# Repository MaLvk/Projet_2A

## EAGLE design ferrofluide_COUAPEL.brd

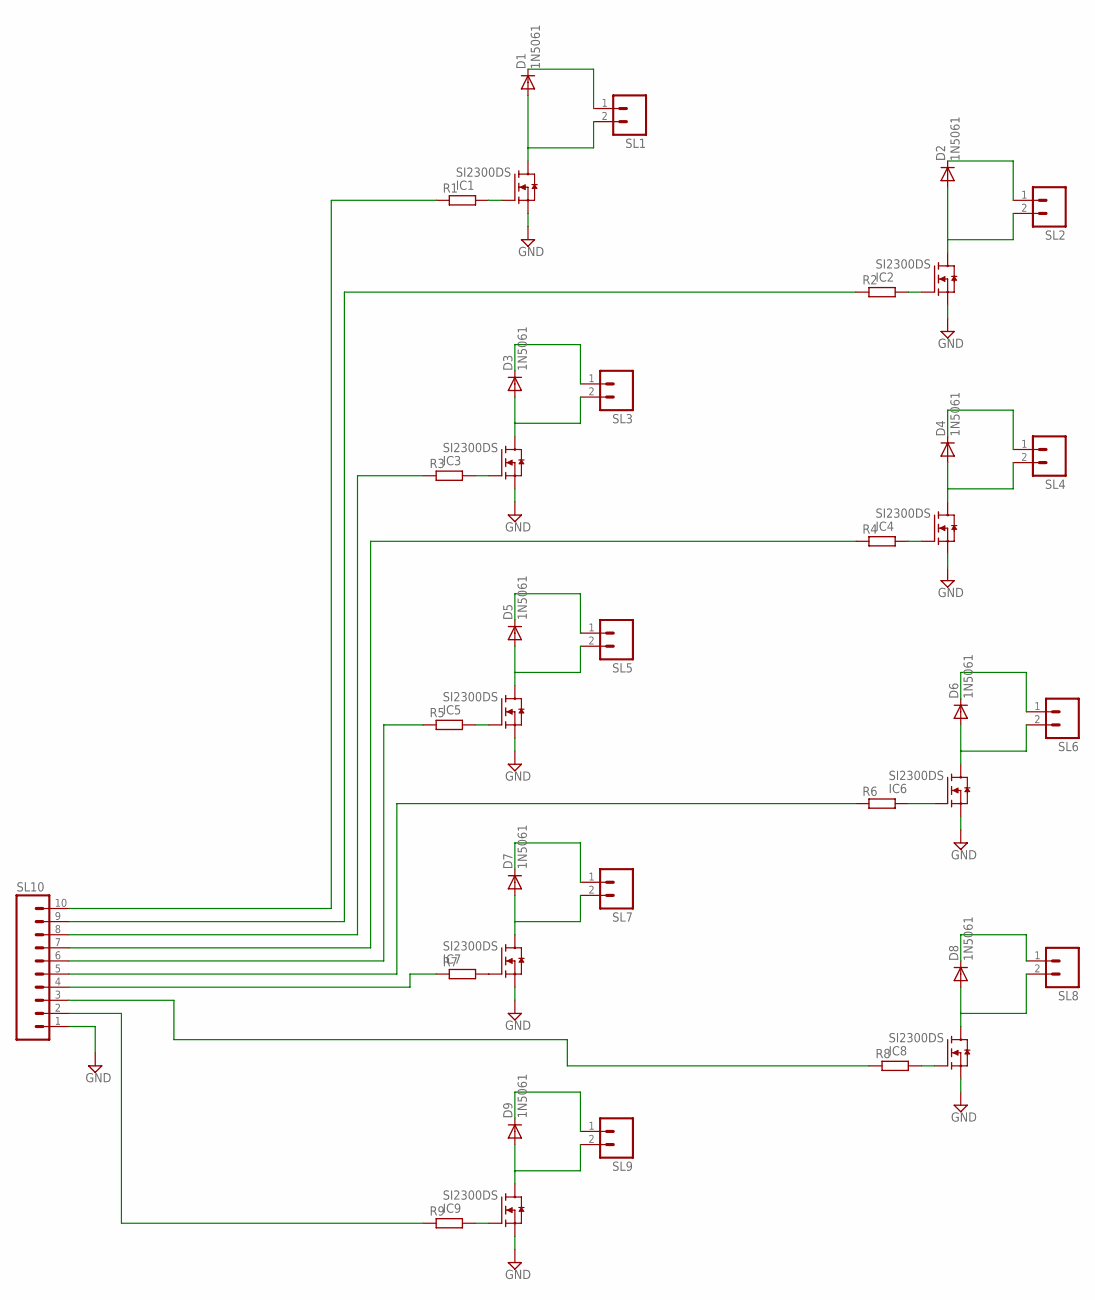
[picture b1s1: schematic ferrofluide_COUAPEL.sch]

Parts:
D1, D2, D3, D4, D5, D6, D7, D8, D9: 1N5061; SOD57-10
IC1, IC2, IC3, IC4, IC5, IC6, IC7, IC8, IC9: SI2300DS; SOT23
R1, R2, R3, R4, R5, R6, R7, R8, R9: R-EU_0207/12; 0207/12
SL1, SL2, SL3, SL4, SL5, SL6, SL7, SL8, SL9: M02; 02P
SL10: M10; 10P

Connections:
GND: IC1.2 (S), IC2.2 (S), IC3.2 (S), IC4.2 (S), IC5.2 (S), IC6.2 (S), IC7.2 (S), IC8.2 (S), IC9.2 (S), SL10.1
unnamed: D1.C, SL1.1
unnamed: D1.A, IC1.3 (D), SL1.2
unnamed: IC1.1 (G), R1.2
unnamed: D2.C, SL2.1
unnamed: D2.A, IC2.3 (D), SL2.2
unnamed: IC2.1 (G), R2.2
unnamed: D4.C, SL4.1
unnamed: D4.A, IC4.3 (D), SL4.2
unnamed: IC4.1 (G), R4.2
unnamed: D6.C, SL6.1
unnamed: D6.A, IC6.3 (D), SL6.2
unnamed: IC6.1 (G), R6.2
unnamed: D8.C, SL8.1
unnamed: D8.A, IC8.3 (D), SL8.2
unnamed: IC8.1 (G), R8.2
unnamed: R9.1, SL10.2
unnamed: D9.C, SL9.1
unnamed: D9.A, IC9.3 (D), SL9.2
unnamed: D7.C, SL7.1
unnamed: IC9.1 (G), R9.2
unnamed: R8.1, SL10.3
unnamed: D7.A, IC7.3 (D), SL7.2
unnamed: IC7.1 (G), R7.2
unnamed: D5.C, SL5.1
unnamed: D5.A, IC5.3 (D), SL5.2
unnamed: IC5.1 (G), R5.2
unnamed: D3.C, SL3.1
unnamed: D3.A, IC3.3 (D), SL3.2
unnamed: IC3.1 (G), R3.2
unnamed: R7.1, SL10.4
unnamed: R6.1, SL10.5
unnamed: R5.1, SL10.6
unnamed: R4.1, SL10.7
unnamed: R3.1, SL10.8
unnamed: R2.1, SL10.9
unnamed: R1.1, SL10.10

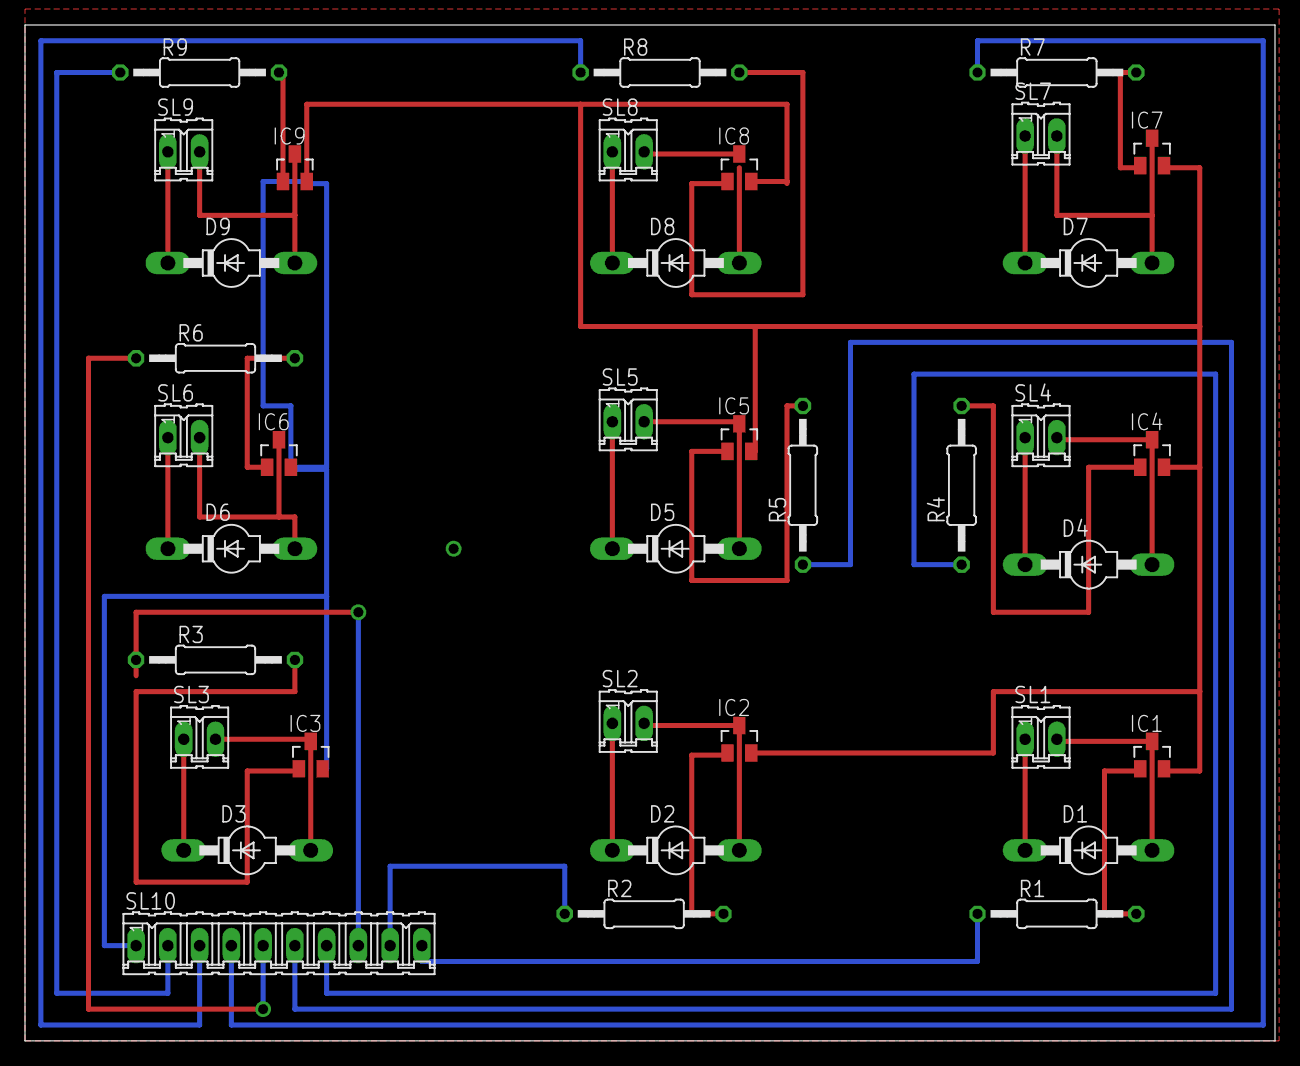
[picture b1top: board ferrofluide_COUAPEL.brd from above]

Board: 2 copper layers, 100.0 x 81.3 mm, 37 parts (0 on the bottom side), 37 nets.

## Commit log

2022-03-08 my first commit
2022-03-08 ajout des vidéos
2022-03-08 ajout de 2 sources ferro, rapport technique et prototypes
2022-03-08 ajout des différentes sections
2022-04-05 Projet ST32
2022-04-08 flow = nouveau projet
    STM32 Flow => standby
    Flow=new project
2022-04-10 Flow projet
    Detecte la fréquence, mais a du mal avec les harmoniques
2022-04-10 Flow -> implémentation par intervalle
    Les modifications se font uniquement dans audio.c
    L'implémentation par intervalle permet de moyenne l'amplitude de la FFT par intervalle de fréquence. Ici, on travaille avec 9 intervalles de 200Hz chacun.
2022-04-11 ajout de ai
    ai=intensite de chaque bande de fréquence de longueur 200Hz
2022-04-24 commit code
    Ajout version final code
2022-04-24 Video test Finaux
2022-04-24 EAGLE
2022-04-25 Tri et ajout vidéos
2022-04-26 Mise à jour du rapport
